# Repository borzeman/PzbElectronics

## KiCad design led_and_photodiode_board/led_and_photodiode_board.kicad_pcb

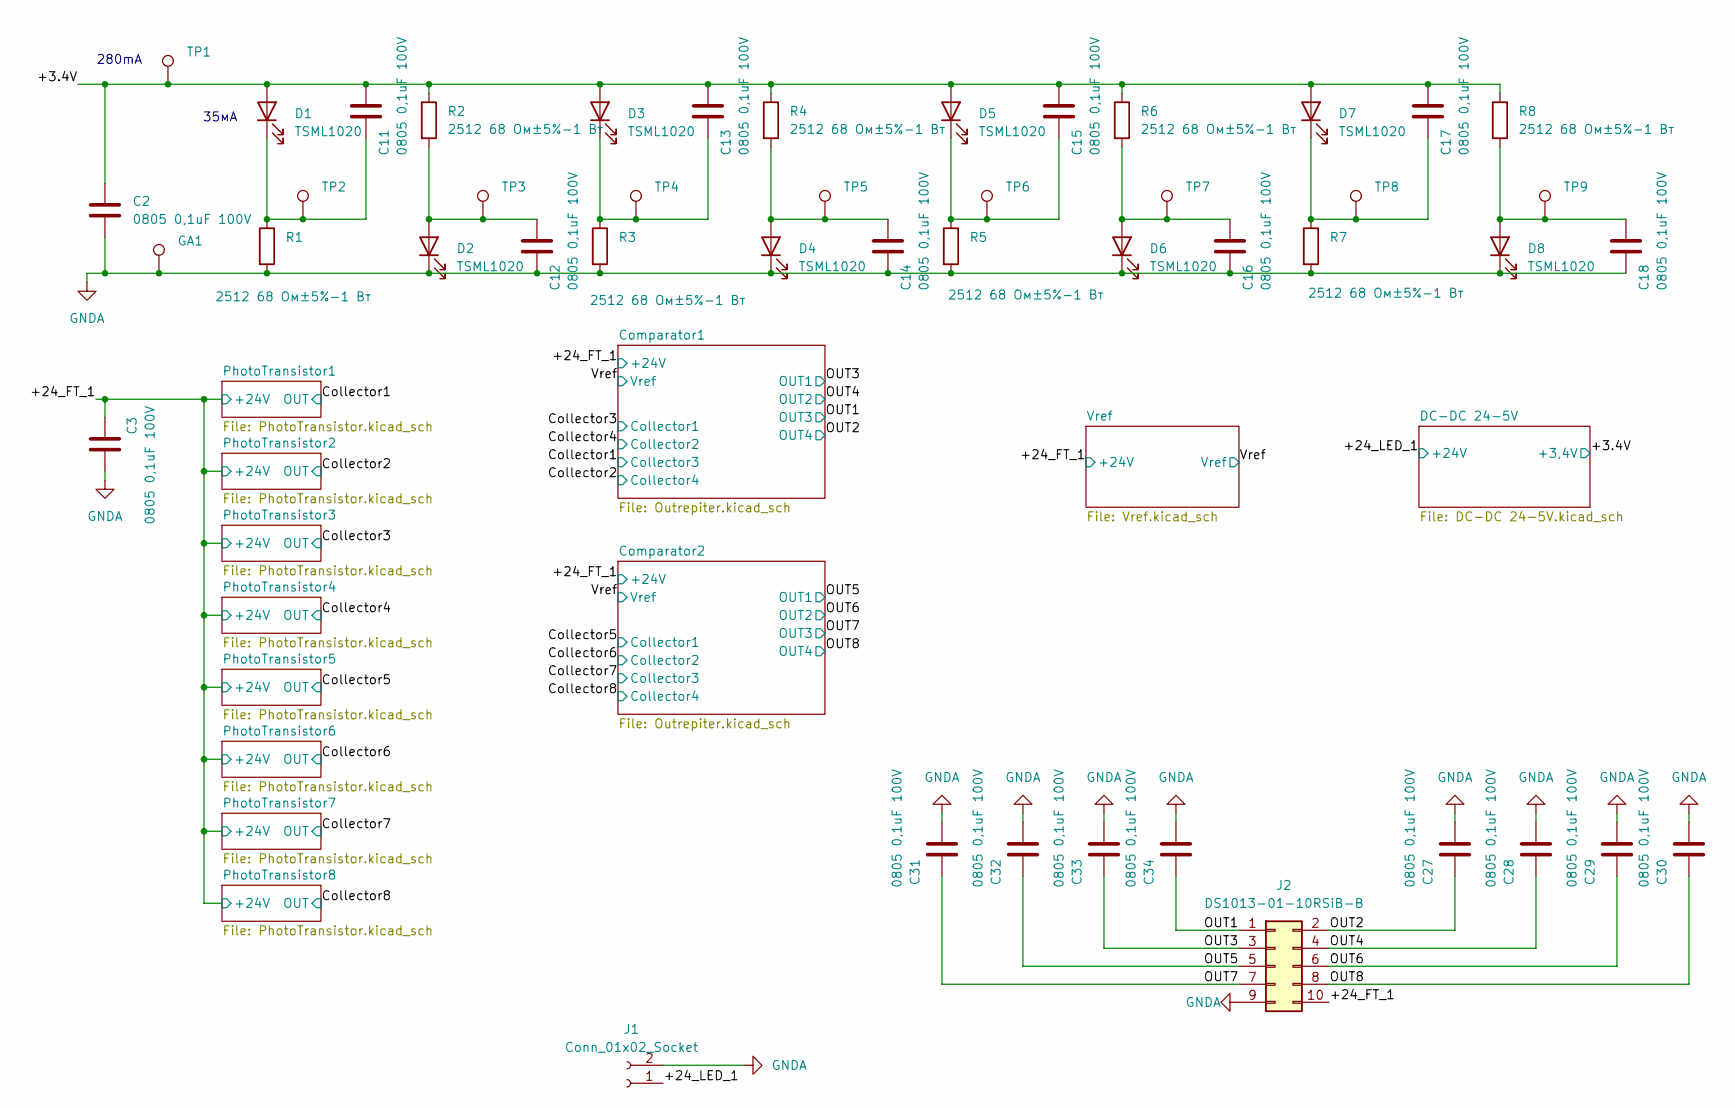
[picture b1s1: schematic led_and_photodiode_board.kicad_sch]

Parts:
C2, C3, C11, C12, C13, C14, C15, C16, C17, C18, C27, C28, C29, C30, C31, C32, C33, C34: 0805 0,1uF 100V; C_0805_2012Metric
D1, D2, D3, D4, D5, D6, D7, D8: TSML1020; D_MiniMELF
GA1: TestPoint; TestPoint_Pad_D1.0mm
J1: Conn_01x02_Socket; SolderWire-0.75sqmm_1x02_P7mm_D1.25mm_OD3.5mm
J2: DS1013-01-10RSiB-B; IDC-Header_2x05_P2.54mm_Horizontal
R1, R2, R3, R4, R5, R6, R7, R8: 2512 68 Ом±5%-1 Вт; R_2512_6332Metric
TP1, TP2, TP3, TP4, TP5, TP6, TP7, TP8, TP9: TestPoint; TestPoint_Pad_D1.0mm

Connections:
/+3.4V: C2.1, C11.1, C13.1, C15.1, C17.1, D1.2 (A), D3.2 (A), D5.2 (A), D7.2 (A), R2.1, R4.1, R6.1, R8.1, TP1.1; also elsewhere on the board
/+24_FT_1: C3.1, J2.10; also elsewhere on the board
/+24_LED_1: J1.1; also elsewhere on the board
/OUT1: C34.1, J2.1; also elsewhere on the board
/OUT2: C27.1, J2.2; also elsewhere on the board
/OUT3: C33.1, J2.3; also elsewhere on the board
/OUT4: C28.1, J2.4; also elsewhere on the board
/OUT5: C32.1, J2.5; also elsewhere on the board
/OUT6: C29.1, J2.6; also elsewhere on the board
/OUT7: C31.1, J2.7; also elsewhere on the board
/OUT8: C30.1, J2.8; also elsewhere on the board
GNDA: C2.2, C3.2, C12.2, C14.2, C16.2, C18.2, C27.2, C28.2, C29.2, C30.2, C31.2, C32.2, C33.2, C34.2, D2.1 (K), D4.1 (K), D6.1 (K), D8.1 (K), GA1.1, J1.2, J2.9, R1.2, R3.2, R5.2, R7.2; also elsewhere on the board
unnamed: C11.2, D1.1 (K), R1.1, TP2.1
unnamed: C12.1, D2.2 (A), R2.2, TP3.1
unnamed: C13.2, D3.1 (K), R3.1, TP4.1
unnamed: C14.1, D4.2 (A), R4.2, TP5.1
unnamed: C15.2, D5.1 (K), R5.1, TP6.1
unnamed: C16.1, D6.2 (A), R6.2, TP7.1
unnamed: C17.2, D7.1 (K), R7.1, TP8.1
unnamed: C18.1, D8.2 (A), R8.2, TP9.1

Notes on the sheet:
35мА
280mA

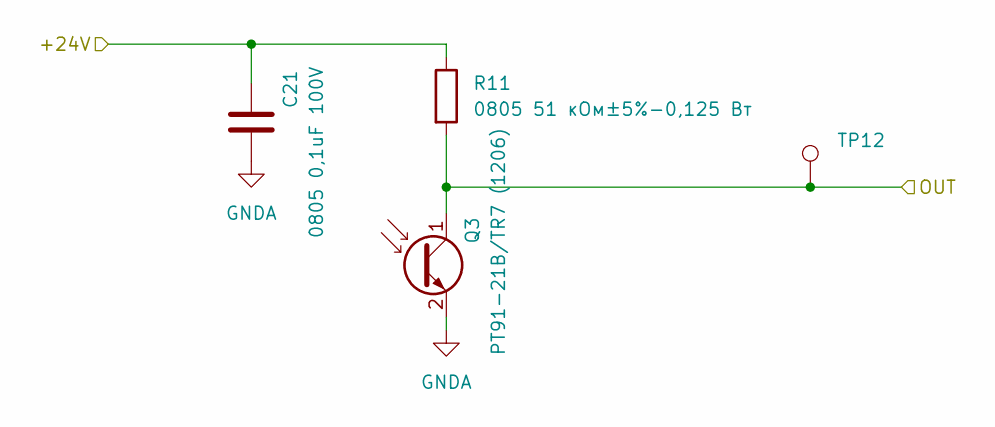
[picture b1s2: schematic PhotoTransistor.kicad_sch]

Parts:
C21: 0805 0,1uF 100V; C_0805_2012Metric
Q3: PT91-21B/TR7 (1206); D_1206_3216Metric_Pad1.42x1.75mm_HandSolder
R11: 0805 51 кОм±5%-0,125 Вт; R_0805_2012Metric
TP12: TestPoint; TestPoint_Pad_D1.0mm

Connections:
/+24_FT_1: C21.1, R11.1; also elsewhere on the board
/Collector3: Q3.1 (C), R11.2, TP12.1; also elsewhere on the board
GNDA: C21.2, Q3.2 (E); also elsewhere on the board

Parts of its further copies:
C19, C20, C22, C23, C24, C25, C26: 0805 0,1uF 100V; C_0805_2012Metric
Q1, Q2, Q4, Q5, Q6, Q7, Q8: PT91-21B/TR7 (1206); D_1206_3216Metric_Pad1.42x1.75mm_HandSolder
R9, R10, R12, R13, R14, R15, R16: 0805 51 кОм±5%-0,125 Вт; R_0805_2012Metric
TP10, TP11, TP13, TP14, TP15, TP16, TP17: TestPoint; TestPoint_Pad_D1.0mm

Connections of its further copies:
/+24_FT_1: C19.1, C20.1, C22.1, C23.1, C24.1, C25.1, C26.1, R9.1, R10.1, R12.1, R13.1, R14.1, R15.1, R16.1; also elsewhere on the board
/Collector1: Q1.1 (C), R9.2, TP10.1; also elsewhere on the board
/Collector2: Q2.1 (C), R10.2, TP11.1; also elsewhere on the board
/Collector4: Q4.1 (C), R12.2, TP13.1; also elsewhere on the board
/Collector5: Q5.1 (C), R13.2, TP14.1; also elsewhere on the board
/Collector6: Q6.1 (C), R14.2, TP15.1; also elsewhere on the board
/Collector7: Q7.1 (C), R15.2, TP16.1; also elsewhere on the board
/Collector8: Q8.1 (C), R16.2, TP17.1; also elsewhere on the board
GNDA: C19.2, C20.2, C22.2, C23.2, C24.2, C25.2, C26.2, Q1.2 (E), Q2.2 (E), Q4.2 (E), Q5.2 (E), Q6.2 (E), Q7.2 (E), Q8.2 (E); also elsewhere on the board

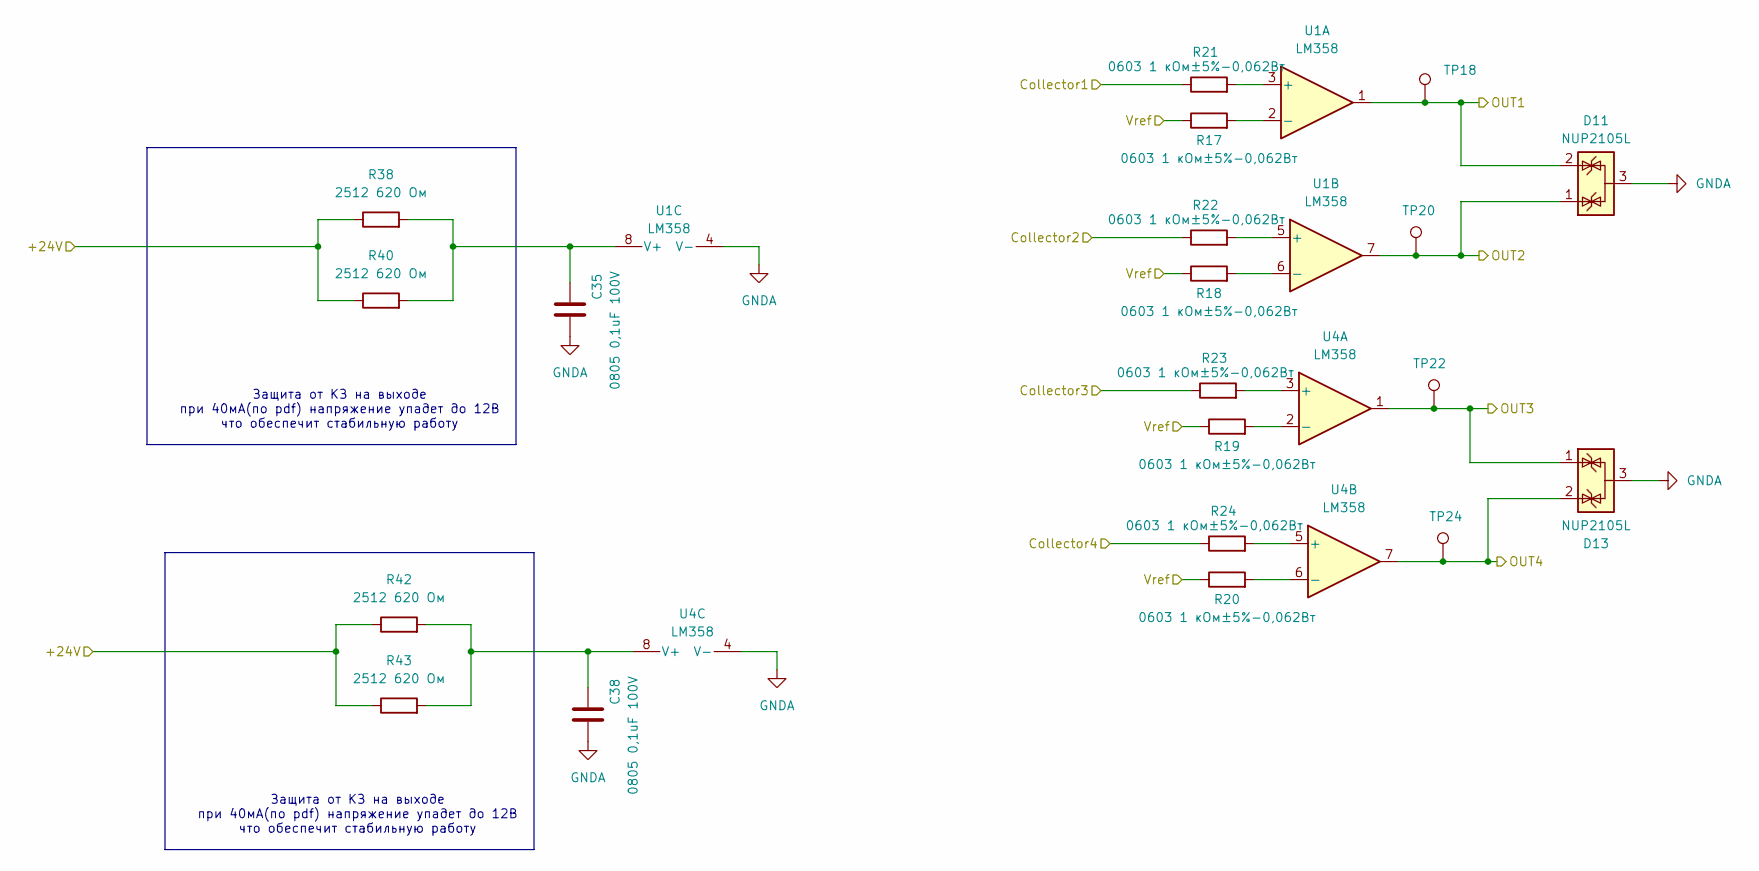
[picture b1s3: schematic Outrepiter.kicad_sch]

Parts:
C35, C38: 0805 0,1uF 100V; C_0805_2012Metric
D11, D13: NUP2105L; SOT-23
R17, R18, R19, R20, R21, R22, R23, R24: 0603 1 кОм±5%-0,062Вт; R_0603_1608Metric
R38, R40, R42, R43: 2512 620 Ом; R_2512_6332Metric
TP18, TP20, TP22, TP24: TestPoint; TestPoint_Pad_D1.0mm
U1, U4: LM358; SOIC-8_3.9x4.9mm_P1.27mm

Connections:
/+24_FT_1: R38.1, R40.1, R42.1, R43.1; also elsewhere on the board
/Collector1: R23.1; also elsewhere on the board
/Collector2: R24.1; also elsewhere on the board
/Collector3: R21.1; also elsewhere on the board
/Collector4: R22.1; also elsewhere on the board
/OUT1: D13.1 (K), TP22.1, U4.1; also elsewhere on the board
/OUT2: D13.2 (K), TP24.1, U4.7; also elsewhere on the board
/OUT3: D11.2 (K), TP18.1, U1.1; also elsewhere on the board
/OUT4: D11.1 (K), TP20.1, U1.7; also elsewhere on the board
/Vref: R17.1, R18.1, R19.1, R20.1; also elsewhere on the board
GNDA: C35.2, C38.2, D11.3 (A), D13.3 (A), U1.4 (V-), U4.4 (V-); also elsewhere on the board
unnamed: R21.2, U1.3 (+)
unnamed: R17.2, U1.2 (-)
unnamed: R22.2, U1.5 (+)
unnamed: R18.2, U1.6 (-)
unnamed: C35.1, R38.2, R40.2, U1.8 (V+)
unnamed: R23.2, U4.3 (+)
unnamed: R19.2, U4.2 (-)
unnamed: R24.2, U4.5 (+)
unnamed: R20.2, U4.6 (-)
unnamed: C38.1, R42.2, R43.2, U4.8 (V+)

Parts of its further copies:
C1, C39: 0805 0,1uF 100V; C_0805_2012Metric
D12, D14: NUP2105L; SOT-23
R25, R26, R27, R28, R29, R30, R31, R32: 0603 1 кОм±5%-0,062Вт; R_0603_1608Metric
R39, R41, R44, R45: 2512 620 Ом; R_2512_6332Metric
TP19, TP21, TP23, TP25: TestPoint; TestPoint_Pad_D1.0mm
U2, U5: LM358; SOIC-8_3.9x4.9mm_P1.27mm

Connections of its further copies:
/+24_FT_1: R39.1, R41.1, R44.1, R45.1; also elsewhere on the board
/Collector5: R25.1; also elsewhere on the board
/Collector6: R27.1; also elsewhere on the board
/Collector7: R29.1; also elsewhere on the board
/Collector8: R31.1; also elsewhere on the board
/OUT5: D12.2 (K), TP19.1, U2.1; also elsewhere on the board
/OUT6: D12.1 (K), TP21.1, U2.7; also elsewhere on the board
/OUT7: D14.1 (K), TP23.1, U5.1; also elsewhere on the board
/OUT8: D14.2 (K), TP25.1, U5.7; also elsewhere on the board
/Vref: R26.1, R28.1, R30.1, R32.1; also elsewhere on the board
GNDA: C1.2, C39.2, D12.3 (A), D14.3 (A), U2.4 (V-), U5.4 (V-); also elsewhere on the board
unnamed: R25.2, U2.3 (+)
unnamed: R26.2, U2.2 (-)
unnamed: R27.2, U2.5 (+)
unnamed: R28.2, U2.6 (-)
unnamed: C1.1, R39.2, R41.2, U2.8 (V+)
unnamed: R29.2, U5.3 (+)
unnamed: R30.2, U5.2 (-)
unnamed: R31.2, U5.5 (+)
unnamed: R32.2, U5.6 (-)
unnamed: C39.1, R44.2, R45.2, U5.8 (V+)

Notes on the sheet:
Защита от КЗ на выходе при 40мА(по pdf) напряжение упадет до 12В что обеспечит стабильную работу

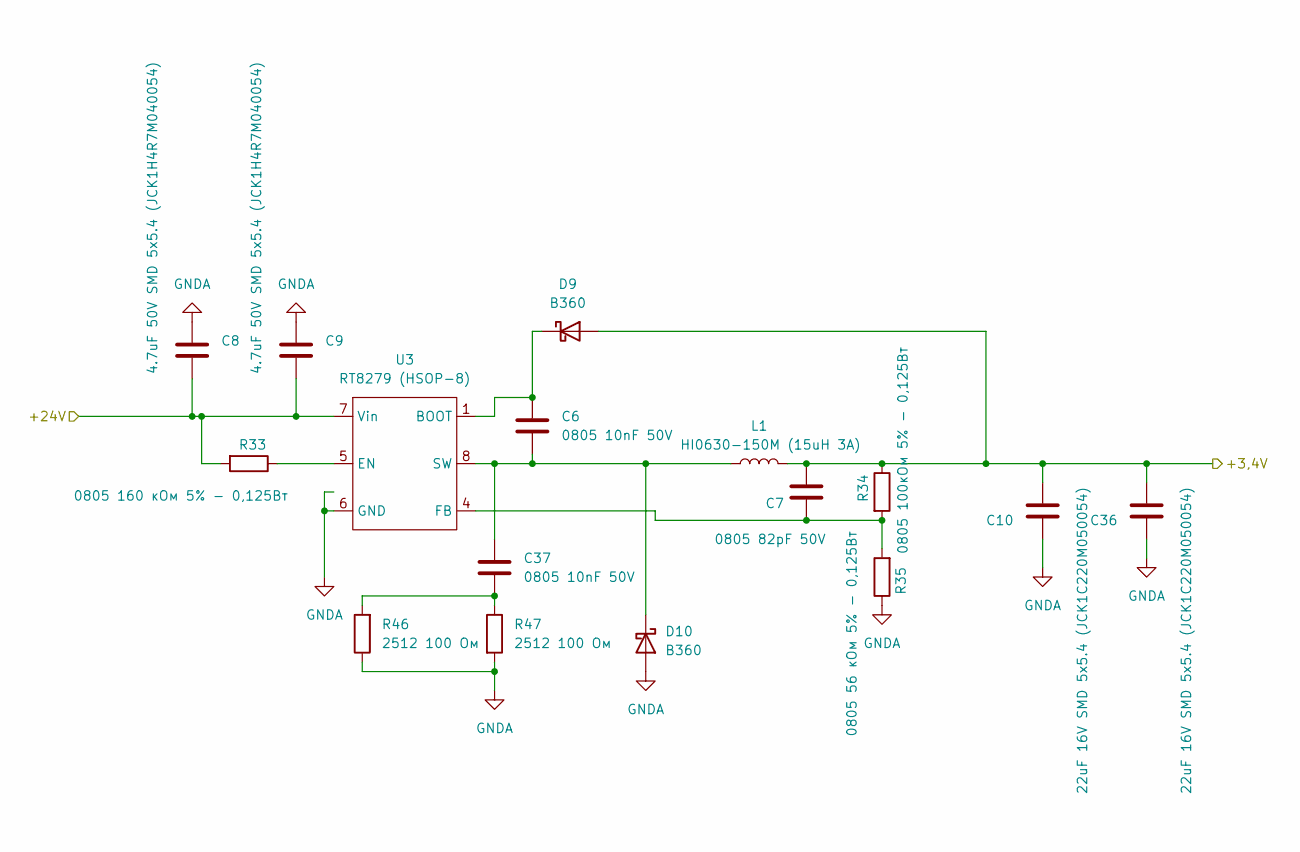
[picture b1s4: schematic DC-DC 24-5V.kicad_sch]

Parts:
C6, C37: 0805 10nF 50V; C_0805_2012Metric
C7: 0805 82pF 50V; C_0805_2012Metric
C8, C9: 4.7uF 50V SMD 5x5.4 (JCK1H4R7M040054); C_Elec_5x5.4
C10, C36: 22uF 16V SMD 5x5.4 (JCK1C220M050054); C_Elec_5x5.4
D9, D10: B360; D_SMC
L1: HI0630-150M (15uH 3A); L_APV_APH0630
R33: 0805 160 кОм 5% - 0,125Вт; R_0805_2012Metric
R34: 0805 100кОм 5% - 0,125Вт; R_0805_2012Metric
R35: 0805 56 кОм 5% - 0,125Вт; R_0805_2012Metric
R46, R47: 2512 100 Ом; R_2512_6332Metric_Pad1.40x3.35mm_HandSolder
U3: RT8279 (HSOP-8); HSOP-8-1EP_3.9x4.9mm_P1.27mm_EP2.41x3.1mm

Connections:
/+3.4V: C7.1, C10.2, C36.2, D9.2 (A), L1.2, R34.1; also elsewhere on the board
/+24_LED_1: C8.2, C9.2, R33.2, U3.7 (Vin); also elsewhere on the board
GNDA: C8.1, C9.1, C10.1, C36.1, D10.2 (A), R35.1, R46.1, R47.2, U3.2 (NC), U3.3 (NC), U3.6 (GND), U3.9 (GND); also elsewhere on the board
unnamed: C37.1, R46.2, R47.1
unnamed: C6.1, D9.1 (K), U3.1 (BOOT)
unnamed: C6.2, C37.2, D10.1 (K), L1.1, U3.8 (SW)
unnamed: R33.1, U3.5 (EN)
unnamed: C7.2, R34.2, R35.2, U3.4 (FB)

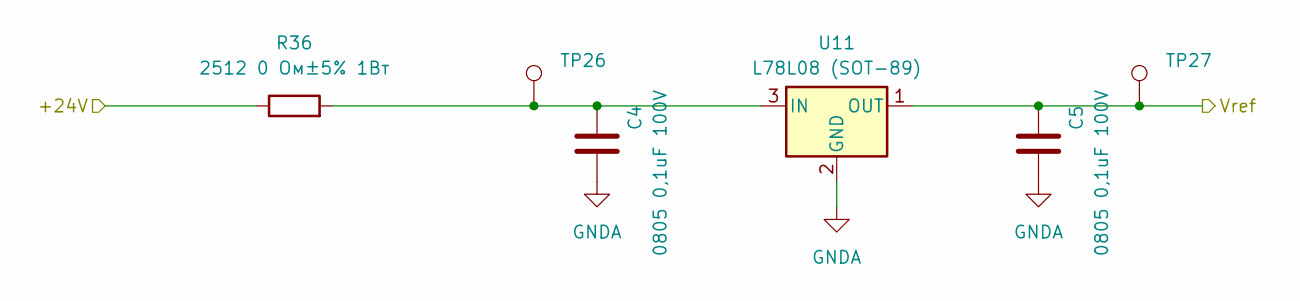
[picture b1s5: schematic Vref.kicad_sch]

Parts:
C4, C5: 0805 0,1uF 100V; C_0805_2012Metric
R36: 2512 0 Ом±5% 1Вт; R_2512_6332Metric
TP26, TP27: TestPoint; TestPoint_Pad_D1.0mm
U11: L78L08 (SOT-89); SOT-89-3

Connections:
/+24_FT_1: R36.1; also elsewhere on the board
/Vref: C5.1, TP27.1, U11.1 (OUT); also elsewhere on the board
GNDA: C4.2, C5.2, U11.2 (GND); also elsewhere on the board
unnamed: C4.1, R36.2, TP26.1, U11.3 (IN)

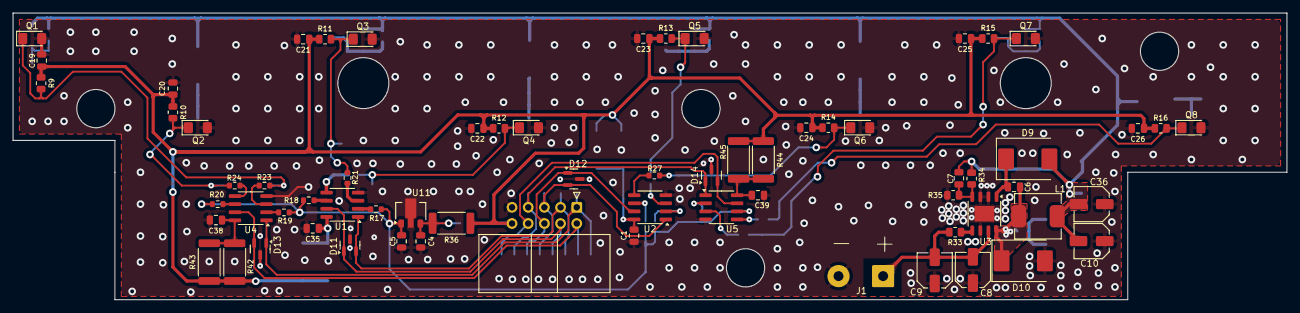
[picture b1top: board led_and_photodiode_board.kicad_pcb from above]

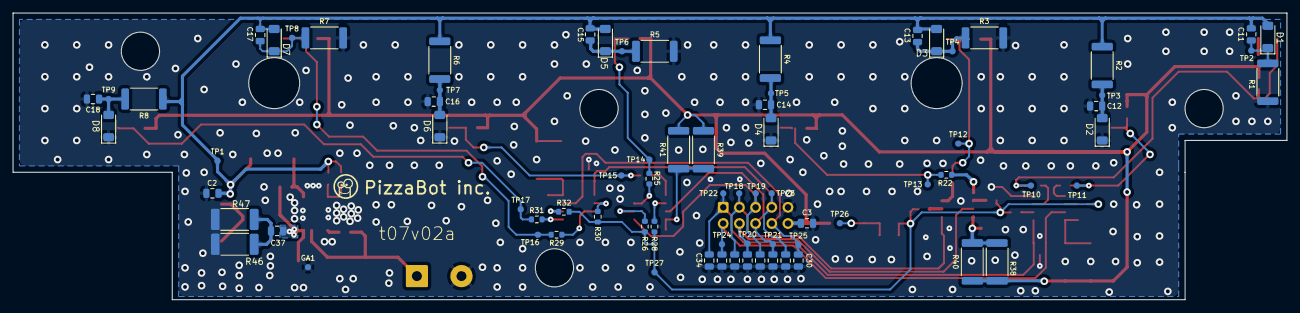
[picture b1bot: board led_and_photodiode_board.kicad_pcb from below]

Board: 2 copper layers, 200.0 x 45.0 mm, 144 parts (77 on the bottom side), 55 nets.

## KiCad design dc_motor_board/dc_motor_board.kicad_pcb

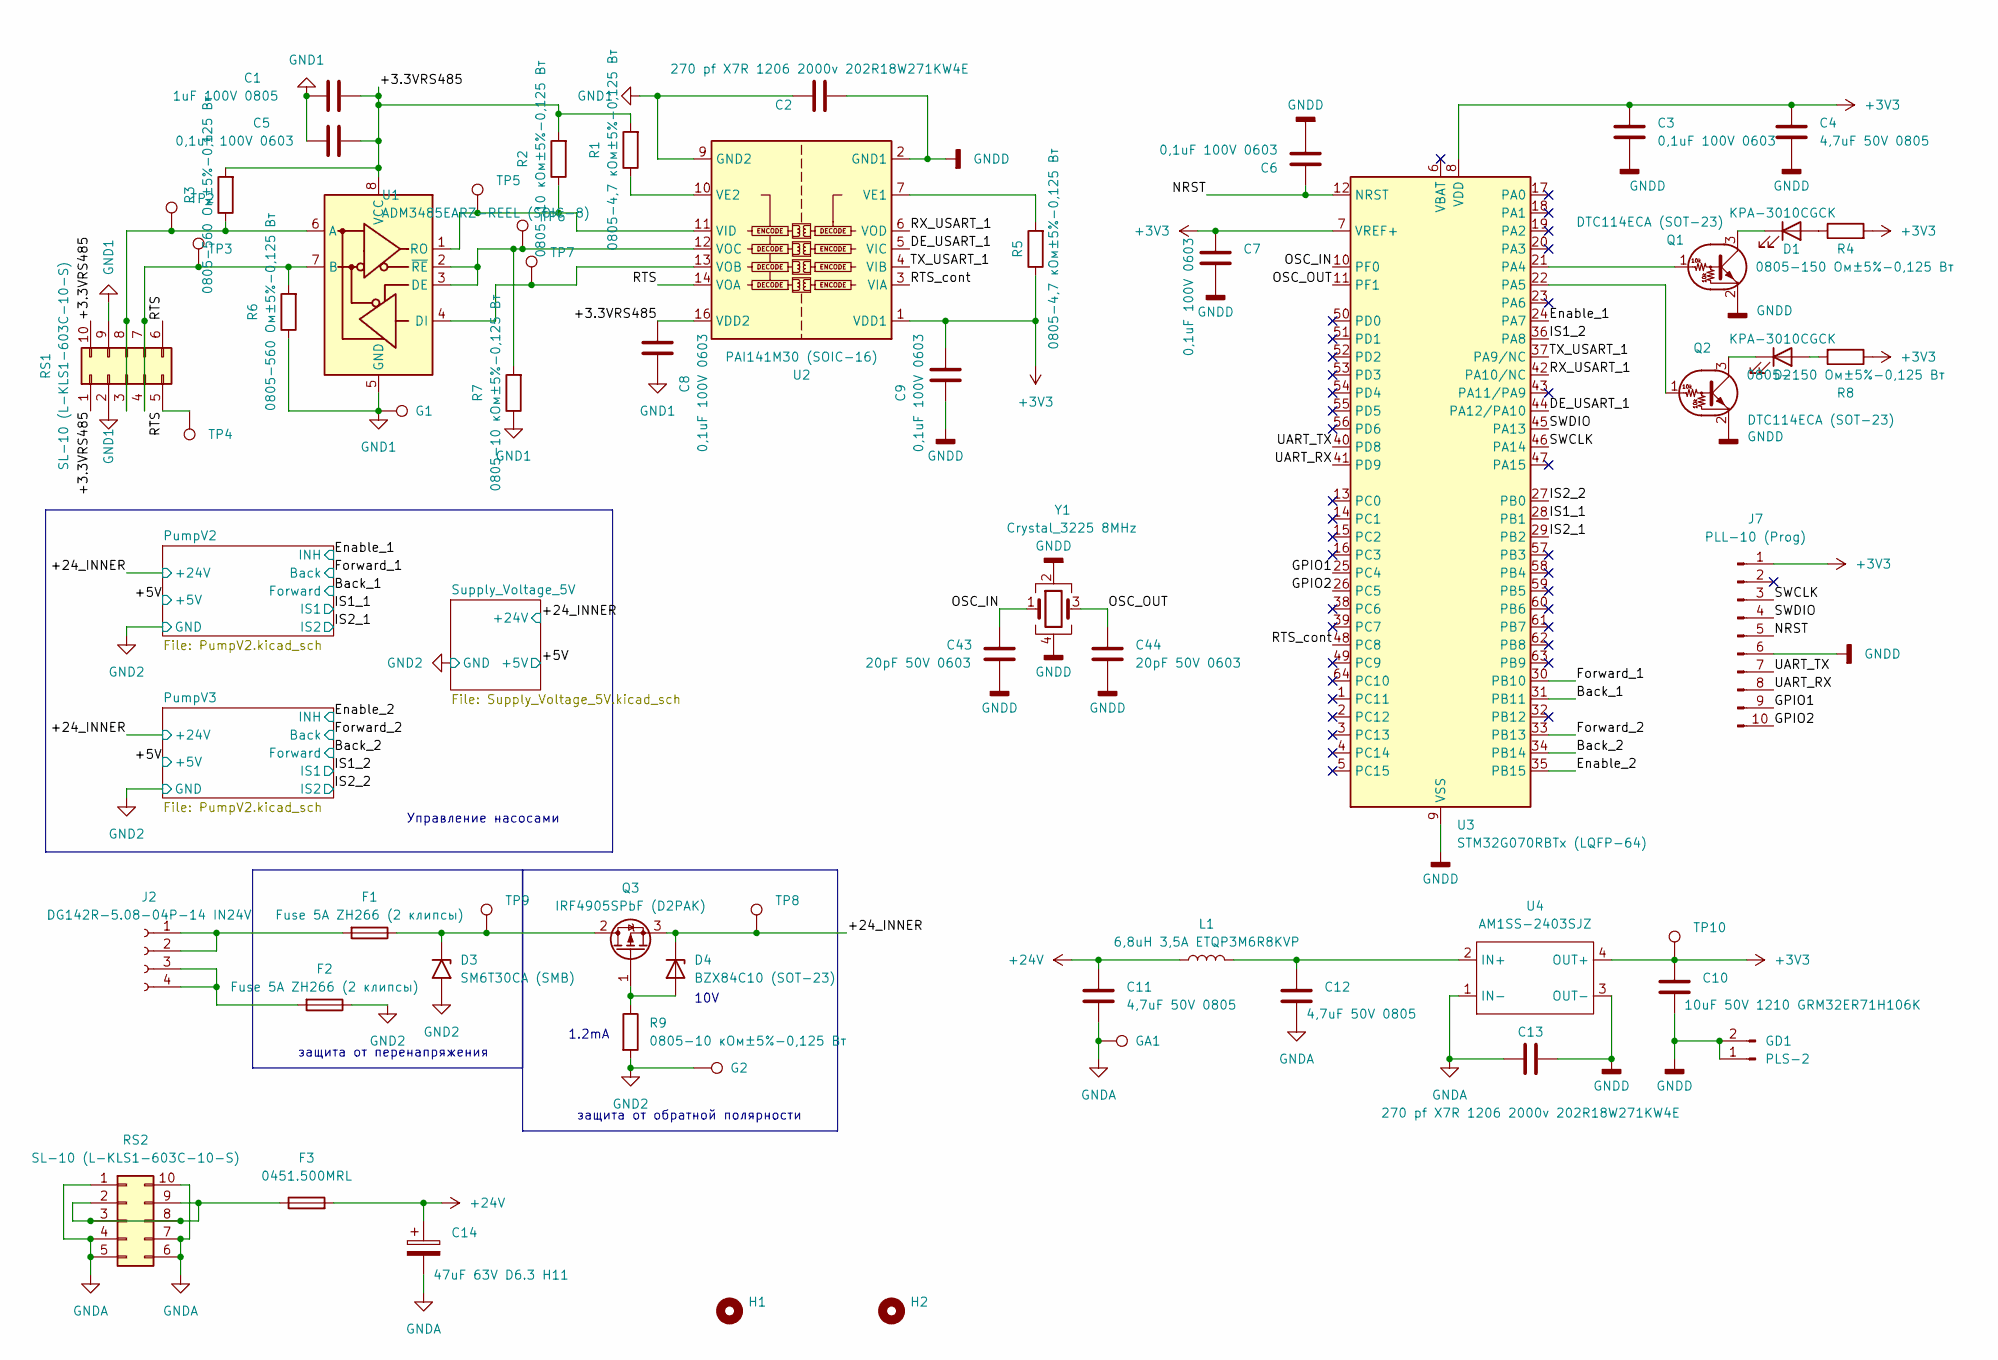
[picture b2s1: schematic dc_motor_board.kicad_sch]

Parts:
C1: 1uF 100V 0805; C_0805_2012Metric
C2, C13: 270 pf X7R 1206 2000v 202R18W271KW4E; C_1210_3225Metric
C3, C5, C6, C7, C8, C9: 0,1uF 100V 0603; C_0603_1608Metric
C4, C11, C12: 4,7uF 50V 0805; C_0805_2012Metric
C10: 10uF 50V 1210 GRM32ER71H106K; C_1210_3225Metric
C14: 47uF 63V D6.3 H11; CP_Radial_D6.3mm_P2.50mm
C43, C44: 20pF 50V 0603; C_0603_1608Metric
D1, D2: KPA-3010CGCK; LED_Kingbright_KPA-3010_3x2x1mm
D3: SM6T30СA (SMB); D_SMB
D4: BZX84C10 (SOT-23); SOT-23
F1, F2: Fuse 5A ZH266 (2 клипсы); Fuseholder_100_series_5x20mm_D1,5
F3: 0451.500MRL; Fuse_Littelfuse-NANO2-451_453
G1, G2: TestPoint; TestPoint_Pad_D1.0mm
GA1: TestPoint; TestPoint_Pad_D1.0mm
GD1: PLS-2; PinHeader_1x02_P2.54mm_Vertical
H1, H2: MountingHole; MountingHole_3.2mm_M3
J2: DG142R-5.08-04P-14 IN24V; DG142R-5.08-04P-14
J7: PLL-10 (Prog); PinHeader_1x10_P1.27mm_Vertical
L1: 6,8uH 3,5A ETQP3M6R8KVP; L_Bourns-SRN6028
Q1, Q2: DTC114ECA (SOT-23); SOT-23
Q3: IRF4905SPbF (D2PAK); TO-263-2
R1, R5: 0805-4,7 кОм±5%-0,125 Вт; R_0805_2012Metric
R2, R7, R9: 0805-10 кОм±5%-0,125 Вт; R_0805_2012Metric
R3, R6: 0805-560 Ом±5%-0,125 Вт; R_0805_2012Metric
R4, R8: 0805-150 Ом±5%-0,125 Вт; R_0805_2012Metric
RS1, RS2: SL-10 (L-KLS1-603C-10-S); Edge_Conn_KLS1-603-10
TP2, TP3, TP4, TP5, TP6, TP7, TP8, TP9, TP10: TestPoint; TestPoint_Pad_D1.0mm
U1: ADM3485EARZ-REEL (SOIC-8); SOIC-8_3.9x4.9mm_P1.27mm
U2: PAI141M30 (SOIC-16); SOIC-16_3.9x9.9mm_P1.27mm
U3: STM32G070RBTx (LQFP-64); LQFP-64_10x10mm_P0.5mm
U4: AM1SS-2403SJZ; Converter_DCDC_Murata_MEE1SxxxxSC_THT
Y1: Crystal_3225 8MHz; Crystal_SMD_TXC_7M-4Pin_3.2x2.5mm

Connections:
+3V3: C3.1, C4.1, C7.1, C9.2, C10.1, J7.1, R4.2, R5.1, R8.1, TP10.1, U2.1 (VDD1), U3.7 (VREF+), U3.8 (VDD), U4.4 (OUT+); also elsewhere on the board
+24V: C11.1, C14.1, F3.2, L1.1
/+3.3VRS485: C1.2, C5.2, C8.2, R1.2, R2.2, R3.2, RS1.1, RS1.10, U1.8 (VCC), U2.16 (VDD2)
/+24_INNER: D4.3 (K), Q3.3 (S), TP8.1; also elsewhere on the board
/Back_1: U3.31 (PB11); also elsewhere on the board
/Back_2: U3.34 (PB14); also elsewhere on the board
/DE_USART_1: U2.5 (VIC), U3.44 (PA12/PA10)
/Enable_1: U3.24 (PA7); also elsewhere on the board
/Enable_2: U3.35 (PB15); also elsewhere on the board
/Forward_1: U3.30 (PB10); also elsewhere on the board
/Forward_2: U3.33 (PB13); also elsewhere on the board
/GPIO1: J7.9, U3.25 (PC4)
/GPIO2: J7.10, U3.26 (PC5)
/IS1_1: U3.28 (PB1); also elsewhere on the board
/IS1_2: U3.36 (PA8); also elsewhere on the board
/IS2_1: U3.29 (PB2); also elsewhere on the board
/IS2_2: U3.27 (PB0); also elsewhere on the board
/NRST: C6.1, J7.5, U3.12 (NRST)
/OSC_IN: C43.1, U3.10 (PF0), Y1.1
/OSC_OUT: C44.1, U3.11 (PF1), Y1.3
/RTS: RS1.5, RS1.6, TP4.1, U2.14 (VOA)
/RTS_cont: U2.3 (VIA), U3.48 (PC8)
/RX_USART_1: U2.6 (VOD), U3.42 (PA10/NC)
/SWCLK: J7.3, U3.46 (PA14)
/SWDIO: J7.4, U3.45 (PA13)
/TX_USART_1: U2.4 (VIB), U3.37 (PA9/NC)
/UART_RX: J7.8, U3.41 (PD9)
/UART_TX: J7.7, U3.40 (PD8)
GND1: C1.1, C2.1, C5.1, C8.1, G1.1, R6.1, R7.1, RS1.2, RS1.9, U1.5 (GND), U2.9 (GND2), U2.15 (GND2)
GND2: D3.2 (A2), F2.1, G2.1, R9.2; also elsewhere on the board
GNDA: C11.2, C12.2, C13.1, C14.2, GA1.1, RS2.1, RS2.4, RS2.5, RS2.6, RS2.7, RS2.10, U4.1 (IN-)
GNDD: C2.2, C3.2, C4.2, C6.2, C7.2, C9.1, C10.2, C13.2, C43.2, C44.2, GD1.1, GD1.2, J7.6, Q1.2 (E), Q2.2 (E), U2.2 (GND1), U2.8 (GND1), U3.9 (VSS), U4.3 (OUT-), Y1.2, Y1.4; also elsewhere on the board
unnamed: D1.2 (A), R4.1
unnamed: D1.1 (K), Q1.3 (C)
unnamed: D2.2 (A), R8.2
unnamed: D2.1 (K), Q2.3 (C)
unnamed: D3.1 (A1), F1.1, Q3.2 (D), TP9.1
unnamed: D4.1 (A), Q3.1 (G), R9.1
unnamed: F1.2, J2.1, J2.2
unnamed: F2.2, J2.3, J2.4
unnamed: Q1.1 (B), U3.21 (PA4)
unnamed: Q2.1 (B), U3.22 (PA5)
unnamed: R3.1, RS1.3, RS1.8, TP2.1, U1.6 (A)
unnamed: R6.2, RS1.4, RS1.7, TP3.1, U1.7 (B)
unnamed: F3.1, RS2.2, RS2.3, RS2.8, RS2.9
unnamed: R7.2, TP6.1, U1.2 (~RE), U1.3 (DE), U2.12 (VOC)
unnamed: TP7.1, U1.4 (DI), U2.13 (VOB)
unnamed: R2.1, TP5.1, U1.1 (RO), U2.11 (VID)
unnamed: R5.2, U2.7 (VE1)
unnamed: R1.1, U2.10 (VE2)
unnamed: C12.1, L1.2, U4.2 (IN+)

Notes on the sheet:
Управление насосами
10V
защита от перенапряжения
1.2mA
защита от обратной полярности

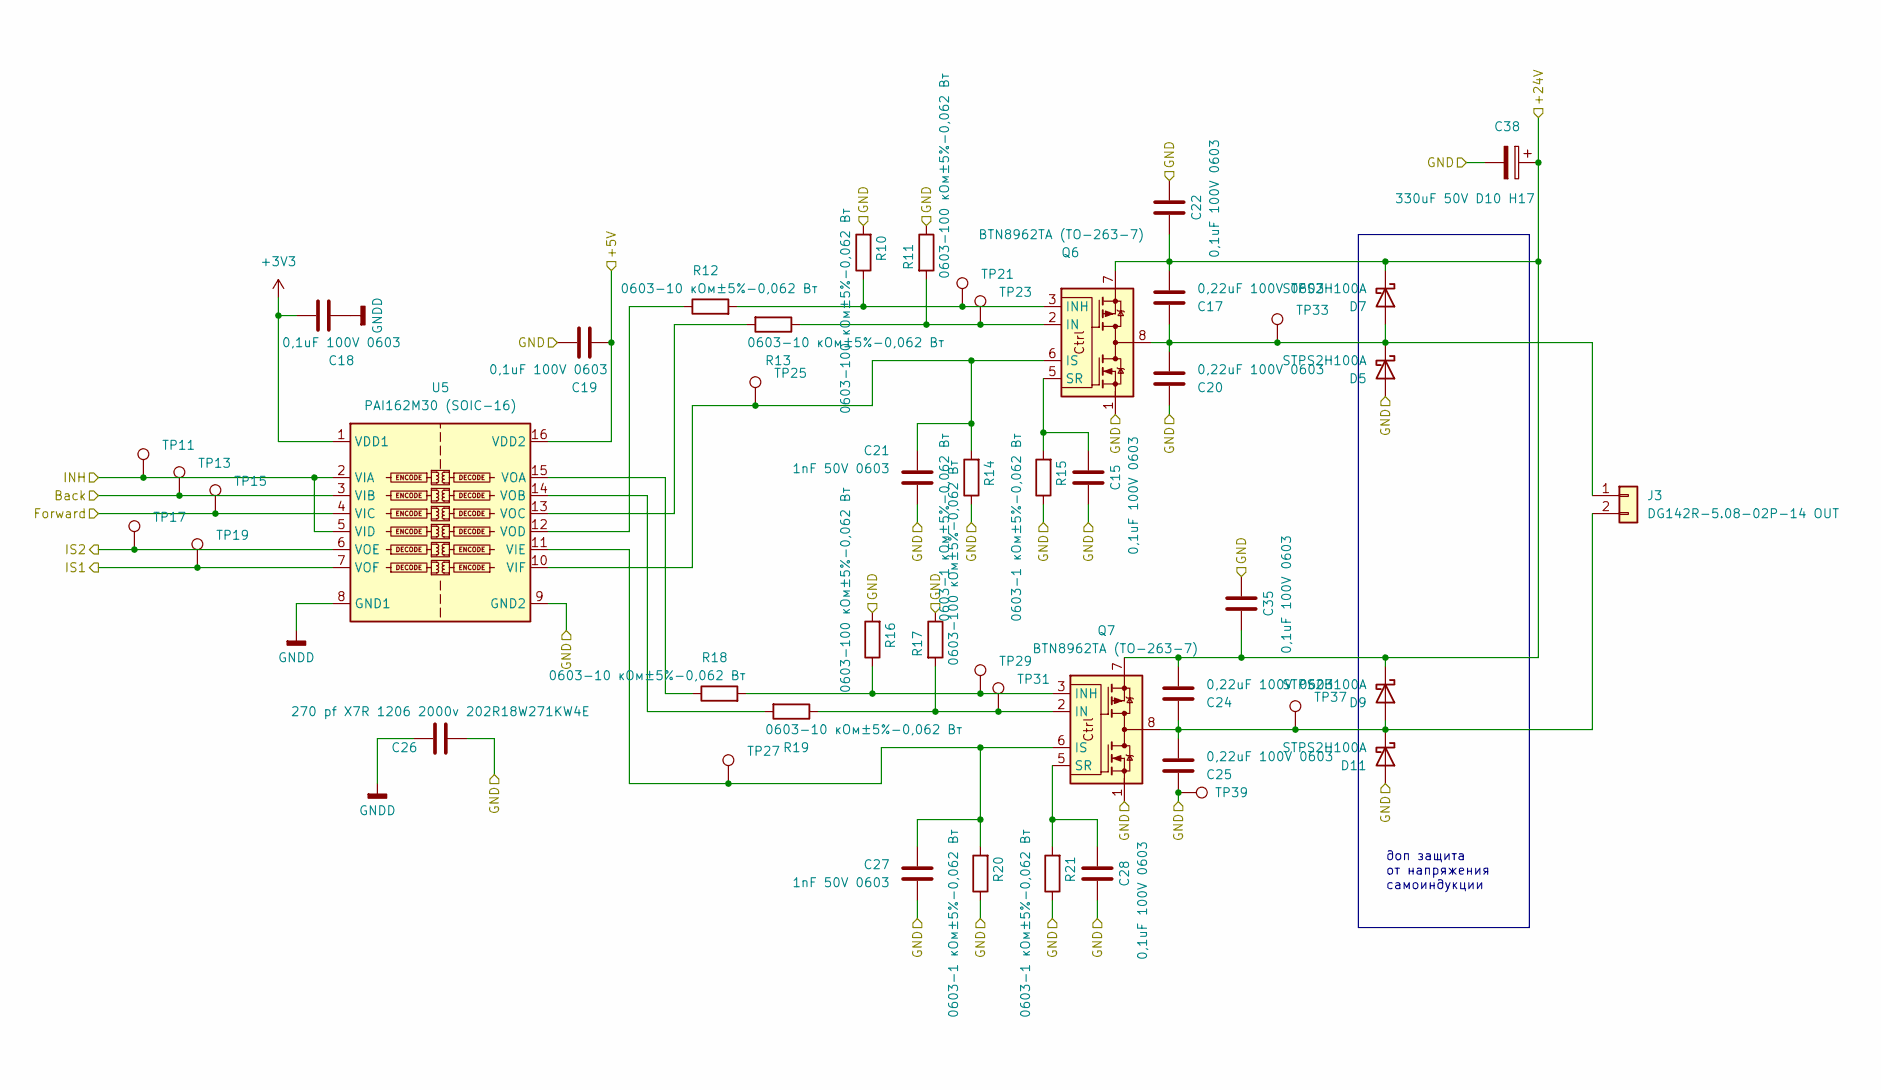
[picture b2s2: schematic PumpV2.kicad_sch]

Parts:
C15, C18, C19, C22, C28, C35: 0,1uF 100V 0603; C_0603_1608Metric
C17, C20, C24, C25: 0,22uF 100V 0603; C_0603_1608Metric_Pad1.08x0.95mm_HandSolder
C21, C27: 1nF 50V 0603; C_0603_1608Metric_Pad1.08x0.95mm_HandSolder
C26: 270 pf X7R 1206 2000v 202R18W271KW4E; C_1210_3225Metric
C38: 330uF 50V D10 H17; CP_Radial_D10.0mm_P5.00mm
D5, D7, D9, D11: STPS2H100A; D_SMA
J3: DG142R-5.08-02P-14 OUT; DG142R-5.08-02P-14
Q6, Q7: BTN8962TA (TO-263-7); TO-263-7_TabPin8
R10, R11, R16, R17: 0603-100 кОм±5%-0,062 Вт; R_0603_1608Metric
R12, R13, R18, R19: 0603-10 кОм±5%-0,062 Вт; R_0603_1608Metric
R14, R15, R20, R21: 0603-1 кОм±5%-0,062 Вт; R_0603_1608Metric
TP11, TP13, TP15, TP17, TP19, TP21, TP23, TP25, TP27, TP29, TP31, TP33, TP37, TP39: TestPoint; TestPoint_Pad_D1.0mm
U5: PAI162M30 (SOIC-16); SOIC-16_3.9x9.9mm_P1.27mm

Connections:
+3V3: C18.2, U5.1 (VDD1); also elsewhere on the board
/+5V: C19.1, U5.16 (VDD2); also elsewhere on the board
/+24_INNER: C17.2, C22.1, C24.2, C35.1, C38.1, D7.1 (K), D9.1 (K), Q6.7, Q7.7; also elsewhere on the board
/Back_2: TP15.1, U5.4 (VIC); also elsewhere on the board
/Enable_2: TP11.1, U5.2 (VIA), U5.5 (VID); also elsewhere on the board
/Forward_2: TP13.1, U5.3 (VIB); also elsewhere on the board
/IS1_2: TP19.1, U5.7 (VOF); also elsewhere on the board
/IS2_2: TP17.1, U5.6 (VOE); also elsewhere on the board
GND2: C15.1, C19.2, C20.1, C21.1, C22.2, C25.1, C26.2, C27.1, C28.1, C35.2, C38.2, D5.2 (A), D11.2 (A), Q6.1, Q7.1, R10.2, R11.1, R14.1, R15.1, R16.2, R17.1, R20.1, R21.1, TP39.1, U5.9 (GND2); also elsewhere on the board
GNDD: C18.1, C26.1, U5.8 (GND1); also elsewhere on the board
unnamed: C17.1, C20.2, D5.1 (K), D7.2 (A), J3.1, Q6.4, Q6.8, TP33.1
unnamed: C24.1, C25.2, D9.2 (A), D11.1 (K), J3.2, Q7.4, Q7.8, TP37.1
unnamed: Q6.2 (IN), R11.2, R13.1, TP23.1
unnamed: Q6.3 (INH), R10.1, R12.2, TP21.1
unnamed: C21.2, Q6.6 (IS), R14.2, TP25.1, U5.10 (VIF)
unnamed: C15.2, Q6.5 (SR), R15.2
unnamed: Q7.2 (IN), R17.2, R19.1, TP31.1
unnamed: Q7.3 (INH), R16.1, R18.2, TP29.1
unnamed: C27.2, Q7.6 (IS), R20.2, TP27.1, U5.11 (VIE)
unnamed: C28.2, Q7.5 (SR), R21.2
unnamed: R18.1, U5.15 (VOA)
unnamed: R19.2, U5.14 (VOB)
unnamed: R13.2, U5.13 (VOC)
unnamed: R12.1, U5.12 (VOD)

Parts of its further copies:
C16, C23, C30, C31, C34, C41: 0,1uF 100V 0603; C_0603_1608Metric
C29, C32, C36, C37: 0,22uF 100V 0603; C_0603_1608Metric_Pad1.08x0.95mm_HandSolder
C33, C46: 1nF 50V 0603; C_0603_1608Metric_Pad1.08x0.95mm_HandSolder
C42: 330uF 50V D10 H17; CP_Radial_D10.0mm_P5.00mm
C45: 270 pf X7R 1206 2000v 202R18W271KW4E; C_1210_3225Metric
D6, D8, D10, D12: STPS2H100A; D_SMA
J4: DG142R-5.08-02P-14 OUT; DG142R-5.08-02P-14
Q4, Q5: BTN8962TA (TO-263-7); TO-263-7_TabPin8
R22, R23, R28, R29: 0603-100 кОм±5%-0,062 Вт; R_0603_1608Metric
R24, R25, R30, R31: 0603-10 кОм±5%-0,062 Вт; R_0603_1608Metric
R26, R27, R32, R33: 0603-1 кОм±5%-0,062 Вт; R_0603_1608Metric
TP12, TP14, TP16, TP18, TP20, TP22, TP24, TP26, TP28, TP30, TP32, TP34, TP38, TP40: TestPoint; TestPoint_Pad_D1.0mm
U6: PAI162M30 (SOIC-16); SOIC-16_3.9x9.9mm_P1.27mm

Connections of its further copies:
+3V3: C30.2, U6.1 (VDD1); also elsewhere on the board
/+5V: C31.1, U6.16 (VDD2); also elsewhere on the board
/+24_INNER: C23.1, C29.2, C36.2, C41.1, C42.1, D8.1 (K), D10.1 (K), Q4.7, Q5.7; also elsewhere on the board
/Back_1: TP16.1, U6.4 (VIC); also elsewhere on the board
/Enable_1: TP12.1, U6.2 (VIA), U6.5 (VID); also elsewhere on the board
/Forward_1: TP14.1, U6.3 (VIB); also elsewhere on the board
/IS1_1: TP20.1, U6.7 (VOF); also elsewhere on the board
/IS2_1: TP18.1, U6.6 (VOE); also elsewhere on the board
GND2: C16.1, C23.2, C31.2, C32.1, C33.1, C34.1, C37.1, C41.2, C42.2, C45.2, C46.1, D6.2 (A), D12.2 (A), Q4.1, Q5.1, R22.2, R23.1, R26.1, R27.1, R28.2, R29.1, R32.1, R33.1, TP40.1, U6.9 (GND2); also elsewhere on the board
GNDD: C30.1, C45.1, U6.8 (GND1); also elsewhere on the board
unnamed: C29.1, C32.2, D6.1 (K), D8.2 (A), J4.1, Q4.4, Q4.8, TP34.1
unnamed: C36.1, C37.2, D10.2 (A), D12.1 (K), J4.2, Q5.4, Q5.8, TP38.1
unnamed: Q4.2 (IN), R23.2, R25.1, TP24.1
unnamed: Q4.3 (INH), R22.1, R24.2, TP22.1
unnamed: C33.2, Q4.6 (IS), R26.2, TP26.1, U6.10 (VIF)
unnamed: C16.2, Q4.5 (SR), R27.2
unnamed: Q5.2 (IN), R29.2, R31.1, TP32.1
unnamed: Q5.3 (INH), R28.1, R30.2, TP30.1
unnamed: C46.2, Q5.6 (IS), R32.2, TP28.1, U6.11 (VIE)
unnamed: C34.2, Q5.5 (SR), R33.2
unnamed: R30.1, U6.15 (VOA)
unnamed: R31.2, U6.14 (VOB)
unnamed: R25.2, U6.13 (VOC)
unnamed: R24.1, U6.12 (VOD)

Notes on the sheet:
доп защита от напряжения самоиндукции

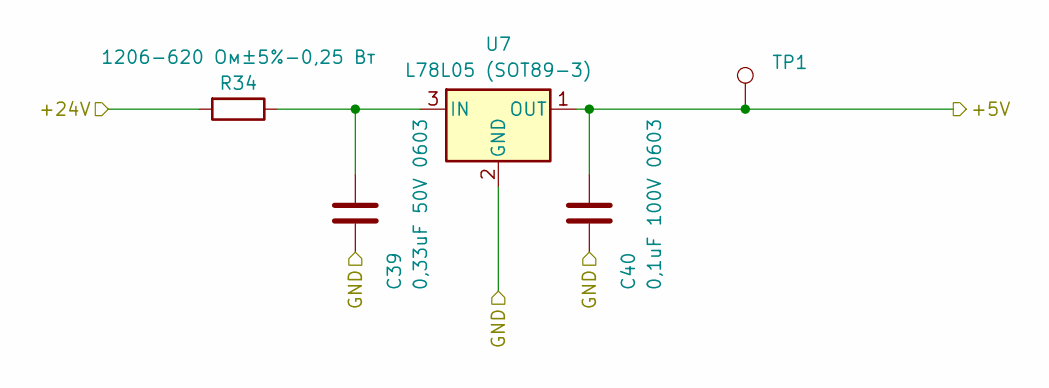
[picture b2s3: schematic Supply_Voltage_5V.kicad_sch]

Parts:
C39: 0,33uF 50V 0603; C_0603_1608Metric_Pad1.08x0.95mm_HandSolder
C40: 0,1uF 100V 0603; C_0603_1608Metric
R34: 1206-620 Ом±5%-0,25 Вт; R_1206_3216Metric
TP1: TestPoint; TestPoint_Pad_D1.0mm
U7: L78L05 (SOT89-3); SOT-89-3

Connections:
/+5V: C40.1, TP1.1, U7.1 (OUT); also elsewhere on the board
/+24_INNER: R34.2; also elsewhere on the board
GND2: C39.2, C40.2, U7.2 (GND); also elsewhere on the board
unnamed: C39.1, R34.1, U7.3 (IN)
